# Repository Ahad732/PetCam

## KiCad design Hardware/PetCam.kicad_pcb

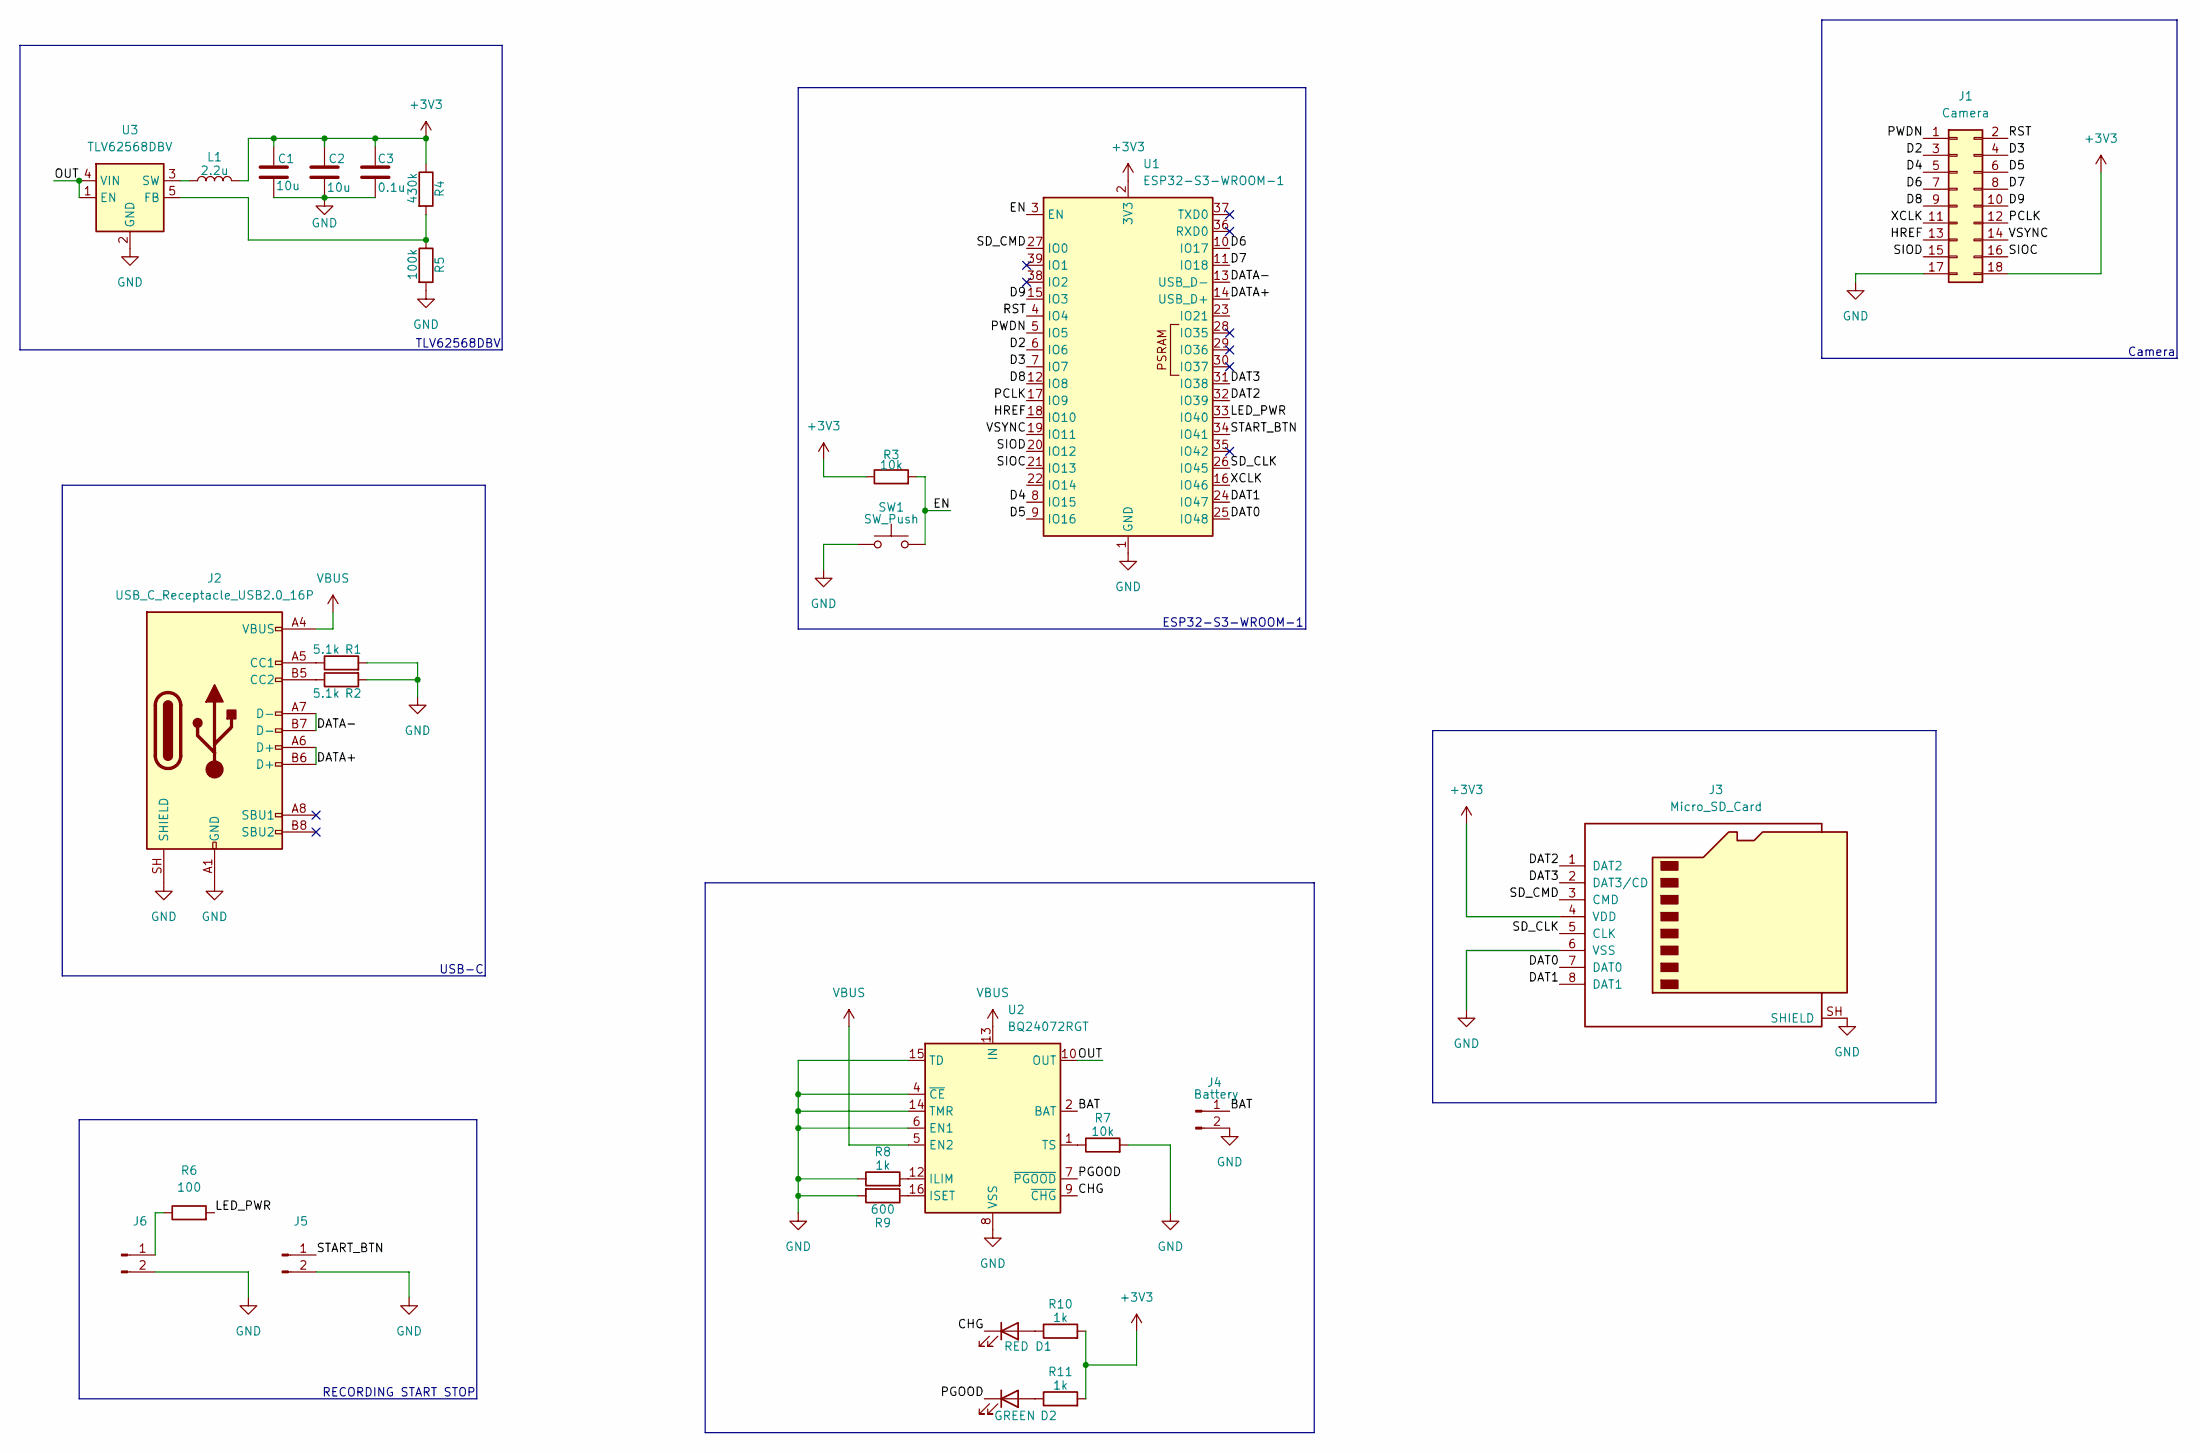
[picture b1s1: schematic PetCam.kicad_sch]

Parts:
C1, C2: 10u; C_0402_1005Metric
C3: 0.1u; C_0402_1005Metric
D1: RED; LED_0402_1005Metric
D2: GREEN; LED_0402_1005Metric
J1: Camera; PinSocket_2x09_P2.54mm_Vertical
J2: USB_C_Receptacle_USB2.0_16P; USB_C_Receptacle_HCTL_HC-TYPE-C-16P-01A
J3: Micro_SD_Card; microSD_HC_Molex_104031-0811
J4: Battery; PinSocket_1x02_P2.54mm_Vertical
J5, J6: Conn_01x02_Pin; PinSocket_1x02_P2.54mm_Vertical
L1: 2.2u; L_Vishay_IFSC-1515AH_4x4x1.8mm
R1, R2: 5.1k; R_0402_1005Metric
R3, R7: 10k; L_0402_1005Metric
R4: 430k; L_0402_1005Metric
R5: 100k; L_0402_1005Metric
R6: 100; R_0402_1005Metric
R8, R10, R11: 1k; L_0402_1005Metric
R9: 600; L_0402_1005Metric
SW1: SW_Push; SW_SPST_PTS810
U1: ESP32-S3-WROOM-1
U2: BQ24072RGT; VQFN-16-1EP_3x3mm_P0.5mm_EP1.6x1.6mm
U3: TLV62568DBV; SOT-23-5

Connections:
+3V3: C1.1, C2.1, C3.1, J1.18, J3.4 (VDD), L1.2, R3.1, R4.1, R10.2, R11.2, U1.2 (3V3)
/BAT: J4.1, U2.2 (BAT), U2.3 (BAT)
/CHG: D1.1 (K), U2.9 (~CHG)
/D2: J1.3, U1.6 (IO6)
/D3: J1.4, U1.7 (IO7)
/D4: J1.5, U1.8 (IO15)
/D5: J1.6, U1.9 (IO16)
/D6: J1.7, U1.10 (IO17)
/D7: J1.8, U1.11 (IO18)
/D8: J1.9, U1.12 (IO8)
/D9: J1.10, U1.15 (IO3)
/DAT0: J3.7 (DAT0), U1.25 (IO48)
/DAT1: J3.8 (DAT1), U1.24 (IO47)
/DAT2: J3.1 (DAT2), U1.32 (IO39)
/DAT3: J3.2 (DAT3/CD), U1.31 (IO38)
/DATA+: J2.A6 (D+), J2.B6 (D+), U1.14 (USB_D+)
/DATA-: J2.A7 (D-), J2.B7 (D-), U1.13 (USB_D-)
/EN: R3.2, SW1.2, U1.3 (EN)
/HREF: J1.13, U1.18 (IO10)
/LED_PWR: R6.2, U1.33 (IO40)
/OUT: U2.10 (OUT), U2.11 (OUT), U3.1 (EN), U3.4 (VIN)
/PCLK: J1.12, U1.17 (IO9)
/PGOOD: D2.1 (K), U2.7 (~PGOOD)
/PWDN: J1.1, U1.5 (IO5)
/RST: J1.2, U1.4 (IO4)
/SD_CLK: J3.5 (CLK), U1.26 (IO45)
/SD_CMD: J3.3 (CMD), U1.27 (IO0)
/SIOC: J1.16, U1.21 (IO13)
/SIOD: J1.15, U1.20 (IO12)
/START_BTN: J5.1, U1.34 (IO41)
/VSYNC: J1.14, U1.19 (IO11)
/XCLK: J1.11, U1.16 (IO46)
GND: C1.2, C2.2, C3.2, J1.17, J2.A1 (GND), J2.A12 (GND), J2.B1 (GND), J2.B12 (GND), J2.SH (SHIELD), J3.6 (VSS), J3.SH (SHIELD), J4.2, J5.2, J6.2, R1.2, R2.2, R5.2, R7.2, R8.1, R9.2, SW1.1, U1.1 (GND), U1.40 (GND), U1.41 (GND), U2.4 (~CE), U2.6 (EN1), U2.8 (VSS), U2.14 (TMR), U2.15 (TD), U2.17 (VSS), U3.2 (GND)
unnamed: D1.2 (A), R10.1
unnamed: D2.2 (A), R11.1
unnamed: J2.A5 (CC1), R1.1
unnamed: J2.B5 (CC2), R2.1
unnamed: J6.1, R6.1
unnamed: R8.2, U2.12 (ILIM)
unnamed: R9.1, U2.16 (ISET)
unnamed: R7.1, U2.1 (TS)
unnamed: R4.2, R5.1, U3.5 (FB)
unnamed: L1.1, U3.3 (SW)
VBUS: J2.A4 (VBUS), J2.A9 (VBUS), J2.B4 (VBUS), J2.B9 (VBUS), U2.5 (EN2), U2.13 (IN)

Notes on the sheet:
Camera
TLV62568DBV
ESP32-S3-WROOM-1
RECORDING START STOP
USB-C

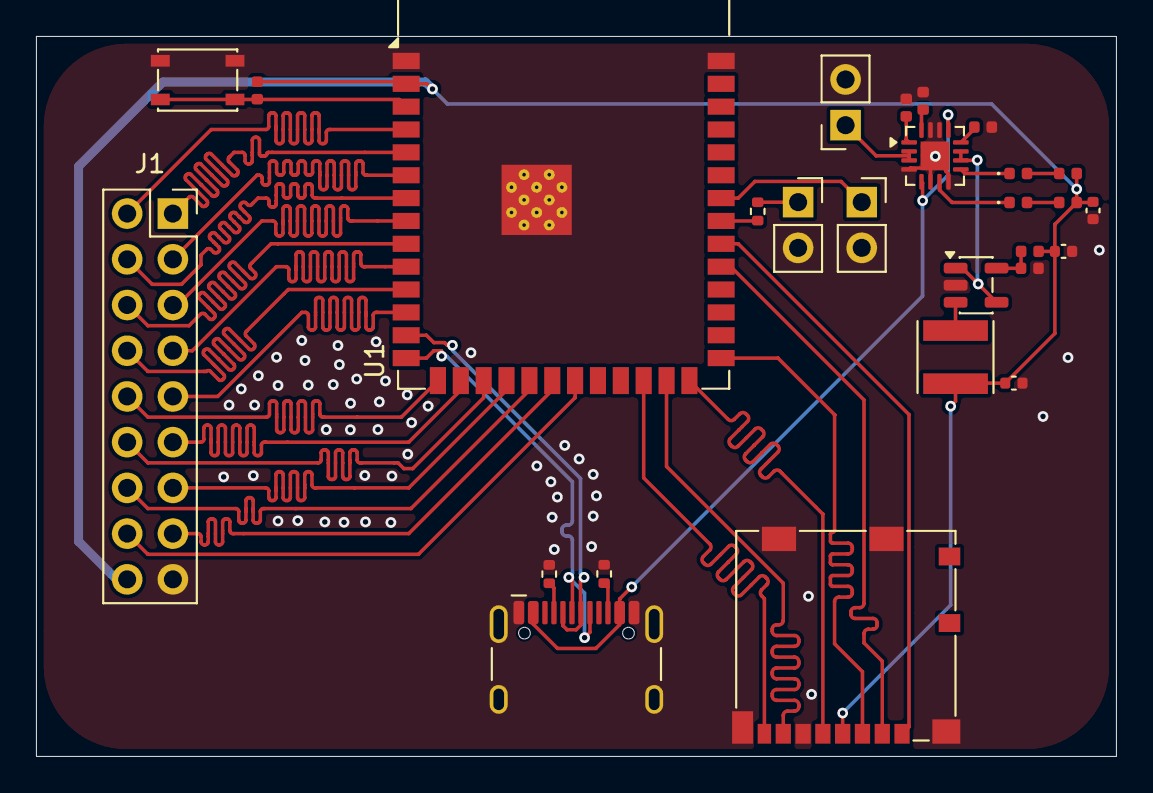
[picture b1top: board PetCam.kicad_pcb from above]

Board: 2 copper layers, 60.0 x 40.0 mm, 27 parts (0 on the bottom side), 44 nets.

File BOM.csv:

Designator,Footprint,Value,Quantity,Price,Link
"C1, C2",402,10u,50,0.93,https://www.lcsc.com/product-detail/C23692971.html
C3,402,0.1u,100,0.15,https://www.lcsc.com/product-detail/C54824947.html
D1,402,RED,50,0.4,https://www.lcsc.com/product-detail/C25503345.html
D2,402,GREEN,50,0.45,https://www.lcsc.com/product-detail/C965793.html
J1,PinSocket_2x09_P2.54mm_Vertical,Camera,1,41.41,https://robu.in/product/waveshare-ov5640-camera-board-c-5-me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
J2,USB_C_Receptacle_HCTL_HC-TYPE-C-16P-01A,USB_C_Receptacle_USB2.0_16P,10,0.53,https://www.lcsc.com/product-detail/C42400252.html
J3,microSD_HC_Molex_104031-0811,Micro_SD_Card,3,2.05,https://www.lcsc.com/product-detail/C585350.html
J4,Battery,2500 mah,2,13.4,https://robu.in/product/wly104050-2500mah-3-7v-single-cell-r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
"J5, J6",PinSocket_1x02_P2.54mm_Vertical,Arcade Button,2,3.17,https://robu.in/product/24mm-led-arcade-button-green/
L1,L_Vishay_IFSC-1515AH_4x4x1.8mm,2.2u,20,0.62,https://www.lcsc.com/product-detail/C55096218.html
"R1, R2",402,5.1k,100,0.06,https://www.lcsc.com/product-detail/C54920813.html
"R10, R11, R8",402,1k,100,0.07,https://www.lcsc.com/product-detail/C49652832.html
"R3, R7",402,10k,100,0.08,https://www.lcsc.com/product-detail/C49652937.html
R4,402,430k,100,0.05,https://www.lcsc.com/product-detail/C54920733.html
R5,402,100k,100,0.05,https://www.lcsc.com/product-detail/C54920733.html
R6,402,100,100,0.06,https://www.lcsc.com/product-detail/C54920716.html
R9,402,600,100,0.08,https://www.lcsc.com/product-detail/C49656019.html
SW1,SW_SPST_PTS810,SW_Push,5,1.84,https://www.lcsc.com/product-detail/C221895.html
U1,ESP32-S3-WROOM-1,ESP32-S3-WROOM-1,2,10.18,https://www.lcsc.com/product-detail/C2913201.html
U2,VQFN-16-1EP_3x3mm_P0.5mm_EP1.6x1.6mm,BQ24072RGT,3,3.18,https://www.lcsc.com/product-detail/C140288.html
U3,SOT-23-5,TLV62568DBV,5,0.38,https://www.lcsc.com/product-detail/C163219.html
,,PCB + Stencil + Shipping,,16.52,
,,Parts Shipping,,5.52,
,,Total,,101.18,
